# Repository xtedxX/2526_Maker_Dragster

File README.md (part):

# 🏎️ DRAGSTER — Maker Option Project

**A fully custom brushless electric dragster built from scratch: custom PCB, STM32 firmware, 3D-printed chassis and Bluetooth telemetry.**

---

## 📋 Table of Contents

- [Project Overview](#project-overview)
- [System Architecture](#system-architecture)
- [Project Structure](#project-structure)
- [Electronic Design](#electronic-design)
- [Software](#software)
- [3D Modelling and Mechanical Aspect](#3d-modelling-and-mechanical-aspect)
- [Known Issues](#known-issues)

---

## 🚀 Project Overview

This project was carried out as part of the **Maker Option** at school. The goal was to design and build a functional brushless electric dragster entirely from scratch, covering every aspect of the engineering process:

- Custom **4-layer PCB** designed in KiCad
- **STM32G431CBU6** microcontroller firmware written in C with STM32CubeIDE
- **Bluetooth** remote control and telemetry via HC-05
- **3D-printed** chassis and mechanical parts designed in Onshape
- **Brushless motor** driven by a commercial ESC via PWM

---

## 🏗️ System Architecture

### 💡 System Block Diagram

The dragster architecture follows a centralized embedded system design with the STM32G431CBU6 microcontroller managing all peripherals, sensor data acquisition, motor control, and wireless communications.

**Key Subsystems:**
- **Flight Computer**: STM32G431CBU6 (ARM Cortex-M4 @ 170 MHz)
- **Sensor Suite**: MMA8452Q 3-axis accelerometer (I²C interface)
- **Human Interface**: TC1602A 16×2 LCD display + WS2812B RGB LED
- **Communications**: HC-05 Bluetooth 2.0 module (UART interface)
- **Motor Control**: Robitronic Razer Ten ESC with built-in BEC driving 3000kV BLDC motor
- **Power**: LiPo 3S (11.1V) → ESC BEC (5V) → Würth 173950378 LDO (3.3V)

### 🔌 Electrical Schematic Overview

The electrical design emphasizes clean power distribution and proper signal isolation between high-current motor traces and sensitive analog sensors.

**Power Distribution:**
- **11.1V LiPo Battery** → **ESC** (Robitronic Razer Ten with built-in BEC)
- **ESC BEC Output (5V @ 3A)** → Würth 173950378 LDO → **3.3V Logic**
- Motor receives 11.1V directly from battery through ESC
- Separate power planes for motor and logic to minimize EMI

**Signal Integrity:**
- I²C bus: 4.7kΩ pull-ups, 400 kHz operation
- UART: 3.3V logic levels, 9600 baud
- PWM: 50 Hz for ESC, 800 kHz for WS2812B
- SWD debug: dedicated JTAG connector

### 🔩 Mechanical Assembly Overview

The mechanical design prioritizes low center of gravity, rear-wheel drive power transfer, and straight-line stability.

**Component Mounting:**
- **Main Chassis**: Flat PLA plate (base structure)
- **Motor Mount**: Rear bracket aligned with drive pulley
- **PCB Mounting**: Center position for balanced weight distribution
- **Wheel Configuration**: Larger rear wheels for traction, smaller front for steering

---

## 📁 Project Structure

```
DRAGSTER/
│
├── 📖 README.md                        # This file
│
├── 🖼️ IMG/                             # Photos of the physical build
│   ├── dragster_assembled.jpg          # Final assembled dragster
│   ├── system_diagram.svg              # System block diagram
│   ├── electrical_schematic.svg        # Electrical schematic
│   ├── mechanical_assembly.svg         # Mechanical assembly diagram
│   ├── pcb_3d_top.png                  # KiCad 3D render top
│   ├── pcb_3d_bottom.png               # KiCad 3D render bottom
│   ├── pcb_real_top.jpg                # Real PCB top view
│   ├── pcb_real_bottom.jpg             # Real PCB bottom view
│   ├── corps_3d.png                    # Dragster body 3D render
│   ├── support_moteur_3d.png           # Motor mount 3D render
│   ├── support_roues_3d.png            # Wheel axle support 3D render
│   └── guide_roues_3d.png             # Lateral wheel guide 3D render
│
├── 📐 CAO/                             # CAD files and design resources
│   ├── DRAGSTER_Cube_MX/               # STM32CubeMX pin configuration project
│   │   └── DRAGSTER_Cube_MX.ioc        # CubeMX IOC file (pin mapping)
│   ├── DRAGSTER_PCB/                   # KiCad PCB project
│   │   ├── DRAGSTER.kicad_pcb          # PCB layout
│   │   ├── DRAGSTER.kicad_sch          # Schematic
│   │   └── ...
│   └── DRAGSTER_3D/                    # Onshape STL exports
│       ├── Corps.stl                   # Dragster body
│       ├── Support_Moteur.stl          # Motor mount
│       ├── Support_roues.stl           # Camshaft / wheel axle support
│       └── Guide_roues.stl             # Lateral wheel guide
│
└── 💻 DRAGSTER_FIRMWARE/               # STM32CubeIDE project
    └── DRAGSTER/
        ├── Core/
        │   ├── Src/
        │   │   ├── main.c              # Application entry point
        │   │   ├── bldc_esc.c          # ESC / brushless motor driver
        │   │   ├── hc05_bt.c           # Bluetooth driver + command parser
        │   │   ├── mma8452q.c          # Accelerometer driver
        │   │   ├── tc1602a_lcd.c       # LCD driver
        │   │   └── ws2812.c            # NeoPixel LED driver
        │   └── Inc/
        │       ├── bldc_esc.h
        │       ├── hc05_bt.h
        │       ├── mma8452q.h
        │       ├── tc1602a_lcd.h
        │       └── ws2812.h
        └── ...
```

---

## ⚡ Electronic Design

### 🔗 Component Selection & Justification

| Component | Model | Specifications | Engineering Rationale |
|-----------|-------|----------------|----------------------|
| **Microcontroller** | STM32G431CBU6 | ARM Cortex-M4, 170 MHz, UFQFPN48, 128 KB Flash, 32 KB RAM, Hardware FPU | High processing speed for real-time sensor fusion and PWM generation; hardware floating-point unit accelerates velocity integration algorithms; 170 MHz provides sufficient headroom for Bluetooth protocol handling |
| **Brushless Motor** | Robitronic Razer Ten 3652 3000kV (R01230) | 3000 kV, 3652 form factor, 3S LiPo compatible, 350W max power | High kV rating provides aggressive acceleration; 3S compatibility matches battery voltage; compact 3652 size fits dragster chassis constraints |
| **ESC** | Robitronic Razer Ten ESC | PWM control 50 Hz, pulse 1–2 ms, waterproof, 60A continuous, **Built-in BEC: 5V @ 3A** | Standard RC PWM interface simplifies firmware; 60A rating provides safety margin for peak current draws; waterproof design protects against track debris; **Built-in BEC eliminates need for separate buck converter — provides 5V power rail for logic** |
| **Accelerometer** | MMA8452Q | 3-axis, 12-bit resolution, I²C interface, ±8g range, 800 Hz ODR, embedded FIFO | ±8g range captures full dragster launch dynamics; 800 Hz sampling rate prevents aliasing of high-frequency vibrations; I²C interface reduces pin count; FIFO buffer offloads MCU during burst acceleration |
| **LCD Display** | TC1602A | 16×2 characters, HD44780 controller, 4-bit parallel interface, 5V tolerant | Industry-standard HD44780 ensures driver compatibility; 4-bit mode saves GPIO pins; 16×2 layout accommodates speed/peak display; high contrast for outdoor visibility |
| **Bluetooth Module** | HC-05 | Bluetooth 2.0 Classic SPP, UART interface, 9600 baud default, 3.3V logic, 10m range | Serial Port Profile (SPP) enables simple UART passthrough; 9600 baud sufficient for telemetry bandwidth; 3.3V logic compatible with STM32 GPIO; widely supported by PC/Android terminals |
| **RGB LED** | WS2812B | Addressable RGB, 800 kHz PWM protocol, 5V supply, single-wire control | Addressable interface allows dynamic status indication; single-wire protocol minimizes pin usage; built-in PWM drivers offload MCU; **Note**: 5V requirement conflicts with 3.3V board supply |
| **Battery** | LiPo 3S | 11.1V nominal (12.6V max, 9V min), 2200 mAh capacity, 25C discharge | 3S voltage matches motor/ESC specifications; 2200 mAh provides ~5 min runtime at full throttle; 25C discharge rating (55A burst) exceeds motor peak current |
| **Voltage Regulator (LDO)** | Würth 173950378 | Input: 4.5–5.5V, Output: 3.3V @ 1A, Dropout: 150mV, Low noise | Converts 5V from ESC BEC to 3.3V logic level; low dropout ensures stable 3.3V even when 5V sags; low noise critical for ADC and analog sensors; compact SOT-23-5 package |
| **Polarity Protection** | SQ2389CES-T1_GE3 | P-channel MOSFET, -20V Vds, -8A Id, 25 mΩ Rds(on) | Low on-resistance minimizes voltage drop; automotive-grade robustness; **Note**: Not populated on final board |

### 📋 PCB Design

The PCB was designed entirely from scratch using **KiCad 9.0**. Before layout, **STM32CubeMX** was used to plan and verify peripheral pin assignments, ensuring no resource conflicts.

**CubeMX Configuration File:**
```
CAO/DRAGSTER_Cube_MX/DRAGSTER_Cube_MX.ioc
```

#### PCB Specifications

| Parameter | Value | Engineering Notes |
|-----------|-------|------------------|
| **Dimensions** | 60 mm × 60 mm | Square form factor simplifies chassis mounting; fits within dragster width constraints |
| **Layer Count** | 4 layers | Minimum for proper power/ground plane separation |
| **Layer 1 (Top)** | Signal routing | Component-side traces, I²C/UART/GPIO |
| **Layer 2 (Inner)** | Ground plane | Solid copper pour, minimal voids, return path for all signals |
| **Layer 3 (Inner)** | Power plane | Split 5V/3.3V regions, thermal relief for vias |
| **Layer 4 (Bottom)** | Signal routing | Secondary traces, connector breakouts |
| **Copper Weight** | 1 oz (35 µm) | Standard weight, adequate for logic-level currents |
| **Min Track/Gap** | 6/6 mil (0.15 mm) | JLCPCB standard capability |
| **Via Size** | 0.3 mm drill, 0.6 mm pad | Standard via, thermal/signal transfer |
| **Manufacturer** | JLCPCB | 4-day turnaround, cost-effective for prototyping |

**Stackup Advantages:**
- Dedicated ground plane (Layer 2) provides low-impedance return path for high-speed PWM signals
- Power plane (Layer 3) reduces supply inductance and decoupling requirements
- Four-layer design enables controlled impedance routing (not critical at these speeds but improves margin)
- Ground plane shields sensitive I²C traces from motor PWM noise

#### KiCad 3D Renders

**Top Layer (Component Side):**

**Component Placement:**
- **Center**: STM32G431CBU6 (UFQFPN-48 package, 7×7 mm)
- **Top-Left**: MMA8452Q accelerometer (QFN-16, oriented with X-axis parallel to chassis)
- **Top-Right**: Würth 173950378 LDO regulator (5V to 3.3V conversion)
- **Bottom-Left**: HC-05 Bluetooth module connector (6-pin header)
- **Bottom-Right**: LCD interface connector (8-pin header: 4 data + RS/E/VCC/GND)
- **Right Edge**: ESC PWM output (3-pin servo connector) + 5V BEC input from ESC
- **Left Edge**: JTAG/SWD debug header (10-pin Cortex standard)

**Bottom Layer (Connector Side):**

**Features:**
- Battery input connector (JST XH 2S/3S balance plug compatible)
- NeoPixel LED footprint (currently unpopulated due to voltage mismatch)
- Reverse polarity protection MOSFET footprint (designed but not populated)
- Ground test points for oscilloscope probing

#### Real PCB Photos

**Fabricated Top Layer:**

**Fabricated Bottom Layer:**

**Fully Assembled Board:**

**Assembly Notes:**
- All SMD components hand-soldered using hot air rework station and an oven
- UFQFPN-48 package required careful alignment and flux application
- 0402 resistors/capacitors used for space efficiency
- Through-hole connectors added last to prevent mechanical stress during SMD soldering

---

## 💻 Software

### 📐 Pin Assignment — STM32CubeMX

Before writing any firmware, **STM32CubeMX** was used to configure the clock tree, assign peripheral pins, and verify that no resource conflicts existed. This tool generates the HAL initialization code automatically, ensuring consistency between hardware and software.

**CubeMX Configuration:**
```
CAO/DRAGSTER_Cube_MX/DRAGSTER_Cube_MX.ioc
```

#### Peripheral Pin Mapping

| Peripheral | Pins | Function | Configuration |
|------------|------|----------|---------------|
| **I2C1** | PA15 (SCL), PB7 (SDA) | MMA8452Q accelerometer communication | 400 kHz fast mode, 7-bit addressing, repeated start enabled |
| **USART2** | PA2 (TX), PA3 (RX) | HC-05 Bluetooth module | 9600 baud, 8N1, RX interrupt-driven |
| **USART1** | PA9 (TX), PA10 (RX) | ST-Link debug console output | 115200 baud, 8N1, polling mode |
| **TIM3 CH1** | PA6 | ESC PWM signal generation | 50 Hz (20 ms period), 1-2 ms pulse width |
| **TIM2 CH4** | PB11 | WS2812B NeoPixel DMA PWM | 800 kHz bit encoding via DMA circular buffer |
| **GPIO Output** | PA8 | LCD RS (Register Select) | Push-pull, high speed |
| **GPIO Output** | PC6 | LCD E (Enable strobe) | Push-pull, high speed |
| **GPIO Output** | PB12–PB15 | LCD DB4–DB7 (4-bit data) | Push-pull, high speed |
| **GPIO Input** | PC13 | Accelerometer INT1 (data ready) | Pull-down, EXTI interrupt (unused in polling implementation) |
| **GPIO Input** | PB9 | Accelerometer INT2 (motion detect) | Pull-down, EXTI interrupt (unused) |

**Clock Configuration:**
- **HSE**: 16 MHz external crystal oscillator
- **PLL**: Input 16 MHz → PLLM /1 → VCO 680 MHz → PLLN ×85 → PLLP /4 → **170 MHz System Clock**
- **APB1**: 85 MHz (TIM2/3 at 170 MHz after prescaler doubling)
- **APB2**: 170 MHz (high-speed peripherals)
- **AHB**: 170 MHz (CPU, DMA, memory)

---

### 🗂️ Firmware Architecture

```
DRAGSTER_FIRMWARE/DRAGSTER/Core/
│
├── Src/
│   ├── main.c              # Application entry point and main loop
│   ├── bldc_esc.c          # Brushless motor ESC PWM driver
│   ├── hc05_bt.c           # HC-05 Bluetooth UART driver and command parser
│   ├── mma8452q.c          # MMA8452Q I²C accelerometer driver
│   ├── tc1602a_lcd.c       # TC1602A LCD parallel interface driver
│   └── ws2812.c            # WS2812B NeoPixel DMA PWM driver (non-functional)
│
└── Inc/
    ├── bldc_esc.h          # ESC API and configuration macros
    ├── hc05_bt.h           # Bluetooth handle and command definitions
    ├── mma8452q.h          # Accelerometer register map and API
    ├── tc1602a_lcd.h       # LCD command macros and API
    └── ws2812.h            # NeoPixel color encoding and API
```

---

### 📦 Software Module Descriptions

#### `main.c` — Application Entry Point

**Responsibilities:**
- HAL library initialization
- System clock configuration (170 MHz)
- Peripheral initialization (GPIO, DMA, timers, UARTs, I²C)
- Boot sequence orchestration
- Main event loop execution

**Boot Sequence:**
1. `HAL_Init()` — Initialize HAL library and configure SysTick timer
2. `SystemClock_Config()` — Configure PLL to achieve 170 MHz system clock
3. `MX_GPIO_Init()` — Configure GPIO pins (LCD control, LEDs, debug)
4. `MX_DMA_Init()` — Initialize DMA channels for TIM2 PWM (NeoPixel)
5. `MX_I2C1_Init()` — Configure I²C1 at 400 kHz for accelerometer
6. `MX_TIM2_Init()` — Configure TIM2 for 800 kHz NeoPixel PWM
7. `MX_TIM3_Init()` — Configure TIM3 for 50 Hz ESC PWM
8. `MX_USART1_UART_Init()` — Configure debug UART at 115200 baud
9. `MX_USART2_UART_Init()` — Configure Bluetooth UART at 9600 baud
10. **`HAL_TIM_PWM_Start(&htim3, TIM_CHANNEL_1)`** — **CRITICAL**: Start ESC PWM immediately (ESC expects signal within 2 seconds of power-on)
11. `LCD_Splash()` — Display boot logo on LCD ("DRAGSTER v1.0")
12. `MMA8452Q_Init()` — Initialize accelerometer (±8g range, 800 Hz ODR)
13. `BT_Init()` — Initialize Bluetooth driver and enable RX interrupt
14. `ESC_Init()` — Execute ESC arming sequence (~8 seconds, blocking)
15. **Main Loop** — `while(1)` calls `BT_Task()` and updates LCD with accelerometer data

**Main Loop Structure:**
```c
while (1) {
    BT_Task();  // Process Bluetooth commands, send telemetry
    
    // Read accelerometer X-axis
    float accel_x_g = MMA8452Q_ReadAccelX();
    
    // Integrate to compute speed (trapezoidal rule)
    static float prev_accel = 0.0f;
    float dt = 0.01f;  // 100 Hz loop rate (approximate)
    speed_ms += (accel_x_g + prev_accel) / 2.0f * 9.81f * dt;
    prev_accel = accel_x_g;
    
    // Update LCD display
    LCD_PrintSpeed(speed_ms * 3.6f);  // Convert m/s to km/h
    LCD_PrintPeakSpeed(peak_speed_kmh);
    
    HAL_Delay(10);  // 100 Hz update rate
}
```

---

#### `bldc_esc.c` / `bldc_esc.h` — ESC PWM Driver

**Purpose:** Generate precise 50 Hz PWM signals to control the Robitronic Razer Ten ESC, which in turn drives the brushless motor.

**Timer Configuration:**
- **Timer**: TIM3 Channel 1 (PA6)
- **Prescaler (PSC)**: 169 → Timer clock = 170 MHz / 170 = **1 MHz** (1 tick = 1 µs)
- **Auto-Reload (ARR)**: 19999 → Period = 20000 µs = **20 ms** = **50 Hz**
- **Pulse Width Range**: 1000–2000 µs (standard RC servo range)

**Verified PWM Values:**

| Compare Value | Pulse Width | Duty Cycle | Throttle | ESC Behavior |
|---------------|-------------|------------|----------|--------------|
| `199` | 200 µs | 1% | 0% | Minimum throttle (motor off) |
| `2999` | 3000 µs | 15% | 50% | Neutral (used during arming only) |
| `9999` | 10000 µs | 50% | 100% | Maximum throttle (full power) |

**Note:** ESC interprets pulse widths, not duty cycle percentages. The unusual mapping (200 µs = 0%, 10000 µs = 100%) is ESC-specific.

**ESC Arming Sequence** (empirically determined):
1. **Step 1** (4 s): Send 3000 µs pulse → ESC beeps twice, recognizes calibration range
2. **Step 2** (2 s): Send 200 µs pulse → ESC beeps three times, arms motor controller
3. **Step 3** (2 s): Send 3000 µs pulse → ESC ready, motor can now be controlled

**Total arming time**: ~8 seconds (blocking operation during boot)

**API Functions:**

| Function | Parameters | Description |
|----------|-----------|-------------|
| `ESC_Init()` | `void` | Executes the 3-step arming sequence. PWM must already be running via `HAL_TIM_PWM_Start()` before calling. Blocking for 8 seconds. |
| `ESC_SetThrottlePct(pct)` | `uint8_t pct` (0–100) | Sets throttle as percentage. Internally maps to 200–10000 µs pulse range via linear interpolation. |
| `ESC_SetPulse(pulse_us)` | `uint16_t pulse_us` | Directly sets PWM compare value (200–10000 µs). Bypasses percentage mapping for advanced control. |
| `ESC_Stop()` | `void` | Immediately sets throttle to 0% (200 µs pulse). Emergency stop function. |
| `ESC_RampTo(pct, step_ms)` | `uint8_t pct`, `uint16_t step_ms` | Gradually increases or decreases throttle to target percentage with specified step delay. Blocking function. Prevents abrupt torque changes that could flip the dragster. |

**Configuration Macros** (`bldc_esc.h`):
```c
#define ESC_PULSE_MIN_US    199U    // 0% throttle (actually 200 µs, off-by-one from rounding)
#define ESC_PULSE_MAX_US    9999U   // 100% throttle (10000 µs)
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
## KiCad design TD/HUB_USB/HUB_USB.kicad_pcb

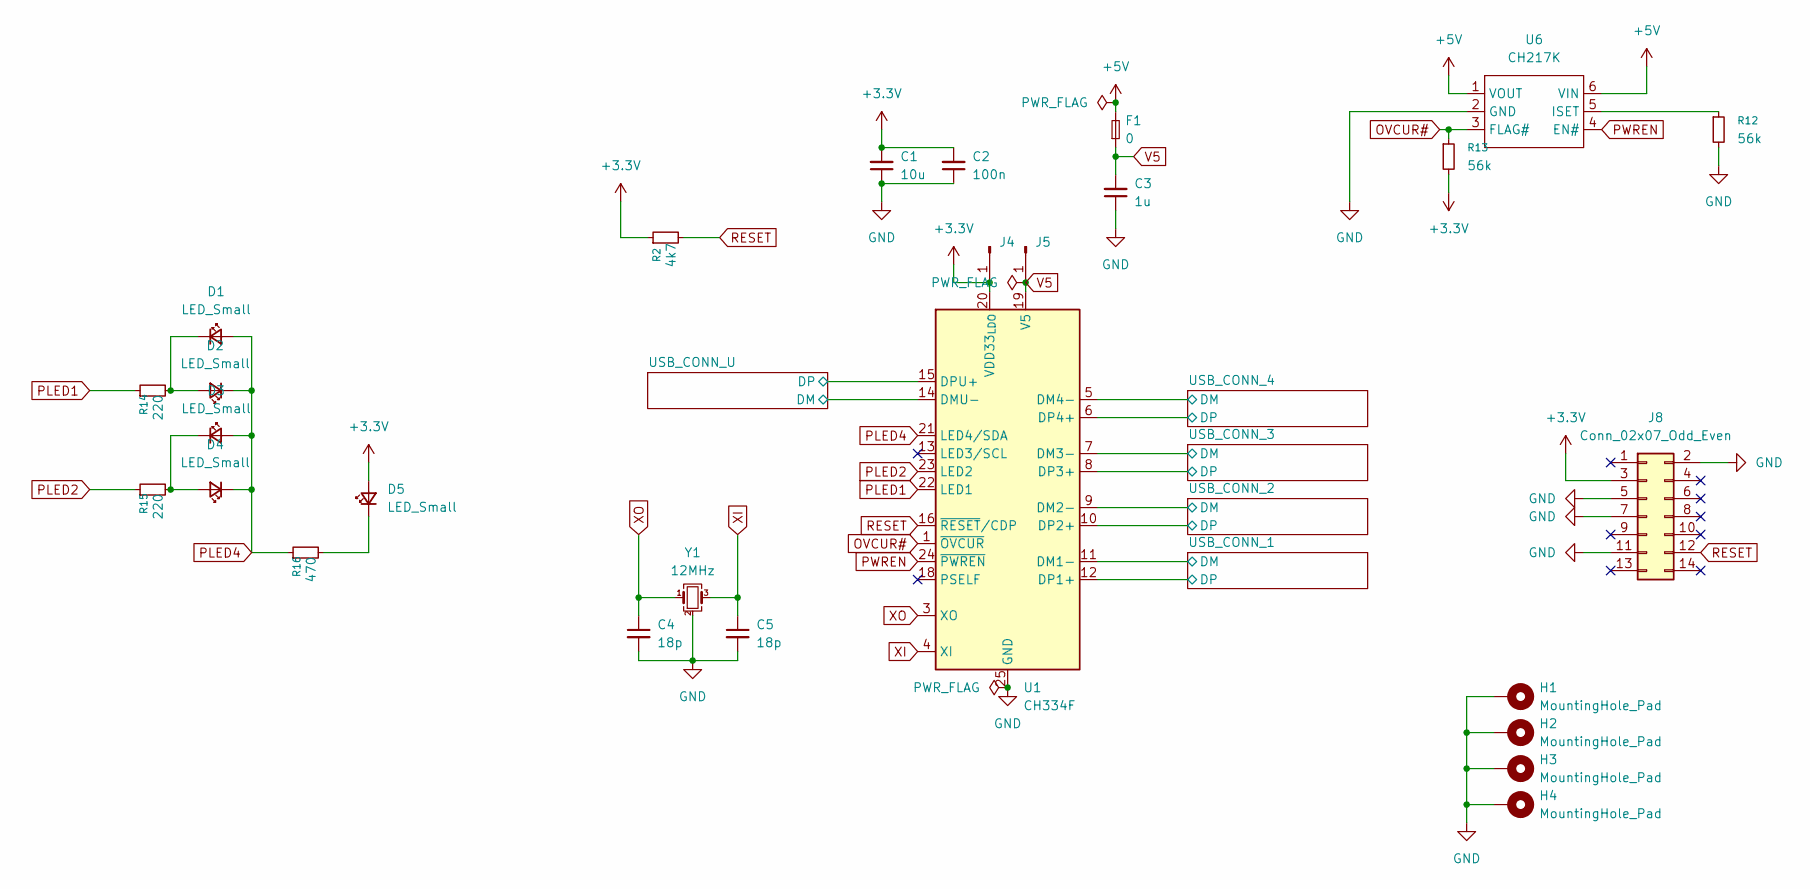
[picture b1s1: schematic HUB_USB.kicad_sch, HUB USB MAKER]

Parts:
C1: 10u; C_0402_1005Metric; MPN GRM155R60J106ME18D
C2: 100n; C_0402_1005Metric; MPN GXT155R71E104KE01D
C3: 1u; C_0603_1608Metric; MPN KGM15BS60J105KT
C4, C5: 18p; C_0402_1005Metric; MPN VJ0402D180FXCAJ
D1, D2, D3, D4, D5: LED_Small; LED_0603_1608Metric; MPN LSM0603453V
F1: 0; Fuse_1206_3216Metric; MPN SF-1206SA2000R-2
H1, H2, H3, H4: MountingHole_Pad; MountingHole_2.7mm_M2.5_Pad_Via
J4, J5: Conn_01x01_Pin; TestPoint_Pad_D1.5mm; MPN CPG-62-TH-TR
J8: Conn_02x07_Odd_Even; PinHeader_2x07_P1.27mm_Vertical_SMD; MPN 10129381-914001BLF
R2: 4k7; R_0402_1005Metric; MPN RCA04024K70JNED
R12, R13: 56k; R_0805_2012Metric; MPN KTR10EZPF5602
R14, R15: 220; R_0402_1005Metric; MPN KTR25JZPF2200
R16: 470; R_0603_1608Metric; MPN PTN0603E4700BST1
U1: CH334F; QFN-24-1EP_4x4mm_P0.5mm_EP2.7x2.7mm; MPN 5997
U6: CH217K; SOT-23-6; MPN CH217K
Y1: 12MHz; Crystal_SMD_WE_CFPX-104-4Pin_5.0x3.2mm; MPN 830036401

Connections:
+3.3V: C1.2, C2.2, D5.2 (A), J4.1, J8.3, R2.1, R13.2, U1.20 (VDD33_{LDO})
+5V: F1.2, U6.1 (VOUT), U6.6 (VIN); also elsewhere on the board
/USB_CONN_1/DM: U1.11 (DM1-); also elsewhere on the board
/USB_CONN_1/DP: U1.12 (DP1+); also elsewhere on the board
/USB_CONN_2/DM: U1.9 (DM2-); also elsewhere on the board
/USB_CONN_2/DP: U1.10 (DP2+); also elsewhere on the board
/USB_CONN_3/DM: U1.7 (DM3-); also elsewhere on the board
/USB_CONN_3/DP: U1.8 (DP3+); also elsewhere on the board
/USB_CONN_4/DM: U1.5 (DM4-); also elsewhere on the board
/USB_CONN_4/DP: U1.6 (DP4+); also elsewhere on the board
/USB_CONN_U/DM: U1.14 (DMU-); also elsewhere on the board
/USB_CONN_U/DP: U1.15 (DPU+); also elsewhere on the board
GND: C1.1, C2.1, C3.1, C4.2, C5.2, H1.1, H2.1, H3.1, H4.1, J8.2, J8.5, J8.7, J8.11, R12.2, U1.25 (GND), U6.2 (GND), Y1.2 (G), Y1.4 (G); also elsewhere on the board
unnamed: D1.1 (K), D2.2 (A), R14.2
unnamed: D3.1 (K), D4.2 (A), R15.2
unnamed: D5.1 (K), R16.2
unnamed: R12.1, U6.5 (ISET)
OVCUR#: R13.1, U1.1 (~OVCUR), U6.3 (FLAG#)
PLED1: R14.1, U1.22 (LED1)
PLED2: R15.1, U1.23 (LED2)
PLED4: D1.2 (A), D2.1 (K), D3.2 (A), D4.1 (K), R16.1, U1.21 (LED4/SDA)
PWREN: U1.24 (~PWREN), U6.4 (EN#)
RESET: J8.12, R2.2, U1.16 (~RESET/CDP)
V5: C3.2, F1.1, J5.1, U1.19 (V5)
XI: C5.1, U1.4 (XI), Y1.3
XO: C4.1, U1.3 (XO), Y1.1

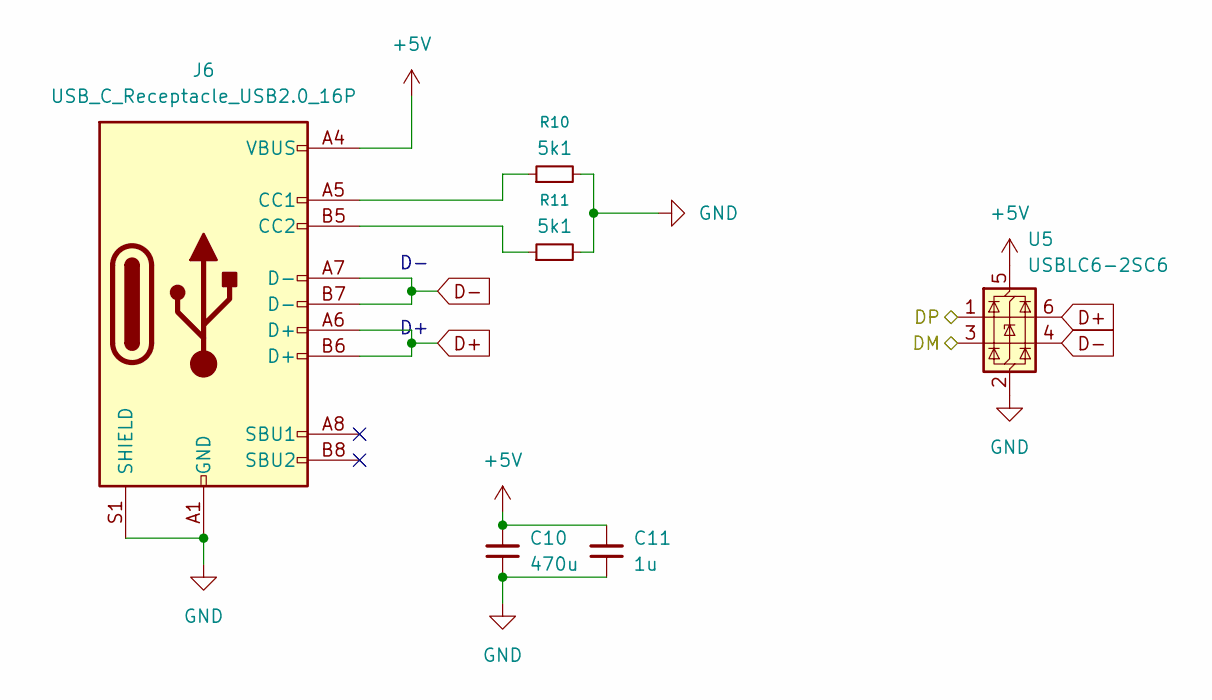
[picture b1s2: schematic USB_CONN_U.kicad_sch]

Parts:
C10: 470u; CP_Elec_6.3x9.9; MPN APZ0609471M010R
C11: 1u; C_0603_1608Metric; MPN KGM15BS60J105KT
J6: USB_C_Receptacle_USB2.0_16P; USB_C_Receptacle_Palconn_UTC16-G; MPN 217179-0001
R10, R11: 5k1; R_0603_1608Metric; MPN TNPW06035K11BYEN
U5: USBLC6-2SC6; SOT-23-6; MPN USBLC6-2SC6

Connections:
+5V: C10.2, C11.2, J6.A4 (VBUS), J6.A9 (VBUS), J6.B4 (VBUS), J6.B9 (VBUS), U5.5 (VBUS); also elsewhere on the board
/USB_CONN_U/DM: U5.3 (I/O2); also elsewhere on the board
/USB_CONN_U/DP: U5.1 (I/O1); also elsewhere on the board
D+: J6.A6 (D+), J6.B6 (D+), U5.6 (I/O1); also elsewhere on the board
D-: J6.A7 (D-), J6.B7 (D-), U5.4 (I/O2); also elsewhere on the board
GND: C10.1, C11.1, J6.A1 (GND), J6.A12 (GND), J6.B1 (GND), J6.B12 (GND), J6.S1 (SHIELD), R10.2, R11.2, U5.2 (GND); also elsewhere on the board
unnamed: J6.A5 (CC1), R10.1
unnamed: J6.B5 (CC2), R11.1

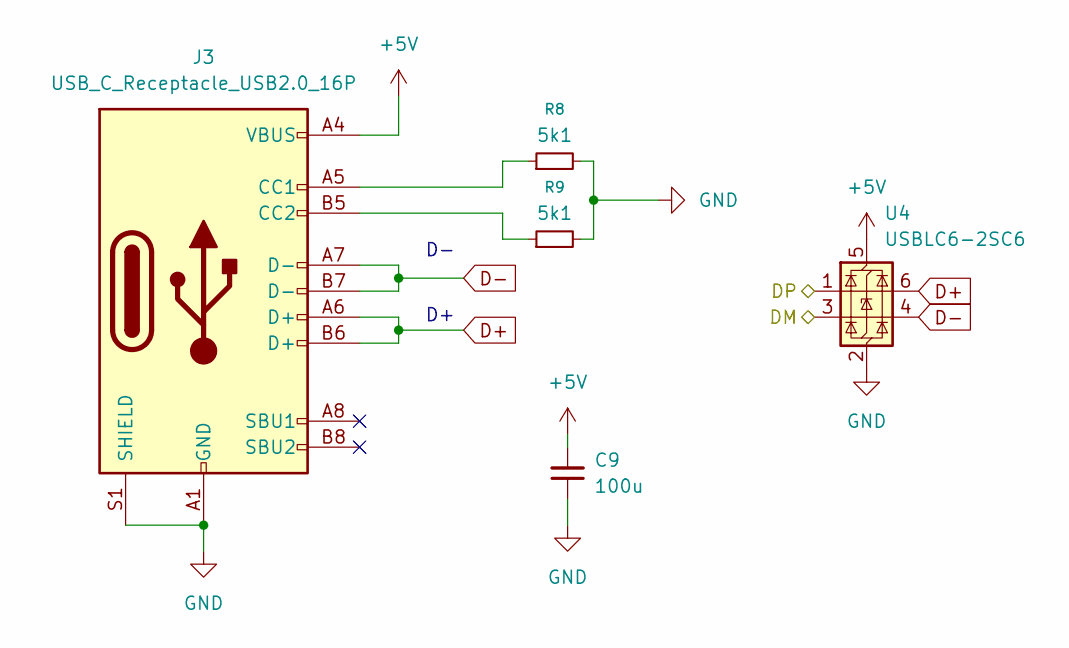
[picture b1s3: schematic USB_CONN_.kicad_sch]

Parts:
C9: 100u; C_1206_3216Metric; MPN KGM31HR50J107MU
J3: USB_C_Receptacle_USB2.0_16P; USB_C_Receptacle_Palconn_UTC16-G; MPN 217179-0001
R8, R9: 5k1; R_0603_1608Metric; MPN TNPW06035K11BYEN
U4: USBLC6-2SC6; SOT-23-6; MPN USBLC6-2SC6

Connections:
+5V: C9.2, J3.A4 (VBUS), J3.A9 (VBUS), J3.B4 (VBUS), J3.B9 (VBUS), U4.5 (VBUS); also elsewhere on the board
/USB_CONN_4/DM: U4.3 (I/O2); also elsewhere on the board
/USB_CONN_4/DP: U4.1 (I/O1); also elsewhere on the board
D+: J3.A6 (D+), J3.B6 (D+), U4.6 (I/O1); also elsewhere on the board
D-: J3.A7 (D-), J3.B7 (D-), U4.4 (I/O2); also elsewhere on the board
GND: C9.1, J3.A1 (GND), J3.A12 (GND), J3.B1 (GND), J3.B12 (GND), J3.S1 (SHIELD), R8.2, R9.2, U4.2 (GND); also elsewhere on the board
unnamed: J3.A5 (CC1), R8.1
unnamed: J3.B5 (CC2), R9.1

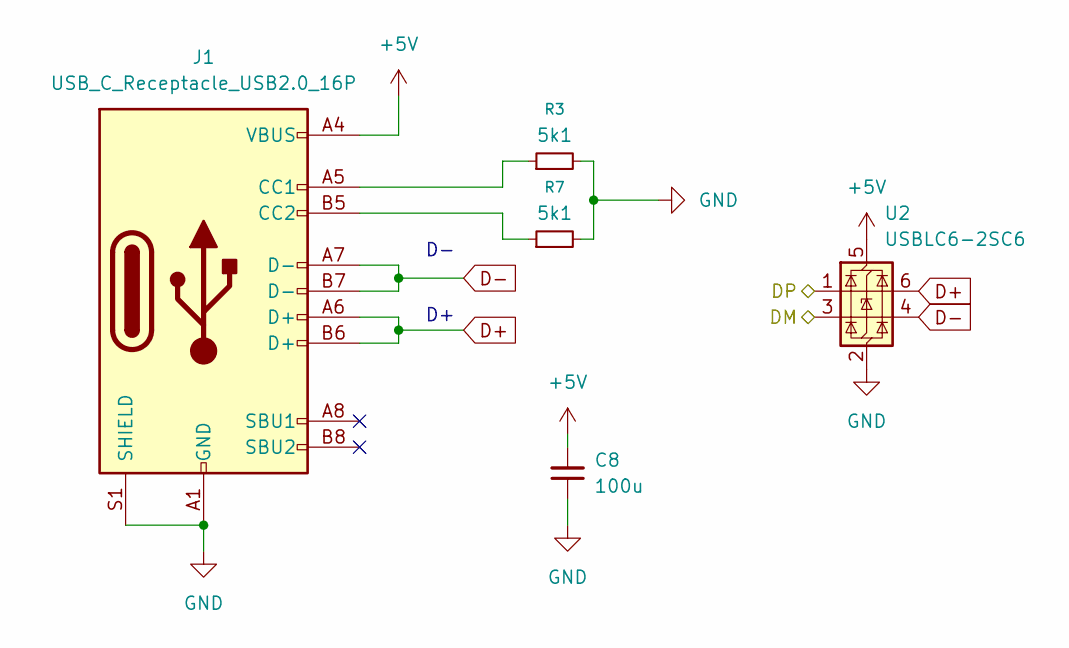
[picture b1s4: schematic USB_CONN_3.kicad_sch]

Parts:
C8: 100u; C_1206_3216Metric; MPN KGM31HR50J107MU
J1: USB_C_Receptacle_USB2.0_16P; USB_C_Receptacle_Palconn_UTC16-G; MPN 217179-0001
R3, R7: 5k1; R_0603_1608Metric; MPN TNPW06035K11BYEN
U2: USBLC6-2SC6; SOT-23-6; MPN USBLC6-2SC6

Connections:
+5V: C8.2, J1.A4 (VBUS), J1.A9 (VBUS), J1.B4 (VBUS), J1.B9 (VBUS), U2.5 (VBUS); also elsewhere on the board
/USB_CONN_3/DM: U2.3 (I/O2); also elsewhere on the board
/USB_CONN_3/DP: U2.1 (I/O1); also elsewhere on the board
D+: J1.A6 (D+), J1.B6 (D+), U2.6 (I/O1); also elsewhere on the board
D-: J1.A7 (D-), J1.B7 (D-), U2.4 (I/O2); also elsewhere on the board
GND: C8.1, J1.A1 (GND), J1.A12 (GND), J1.B1 (GND), J1.B12 (GND), J1.S1 (SHIELD), R3.2, R7.2, U2.2 (GND); also elsewhere on the board
unnamed: J1.A5 (CC1), R3.1
unnamed: J1.B5 (CC2), R7.1

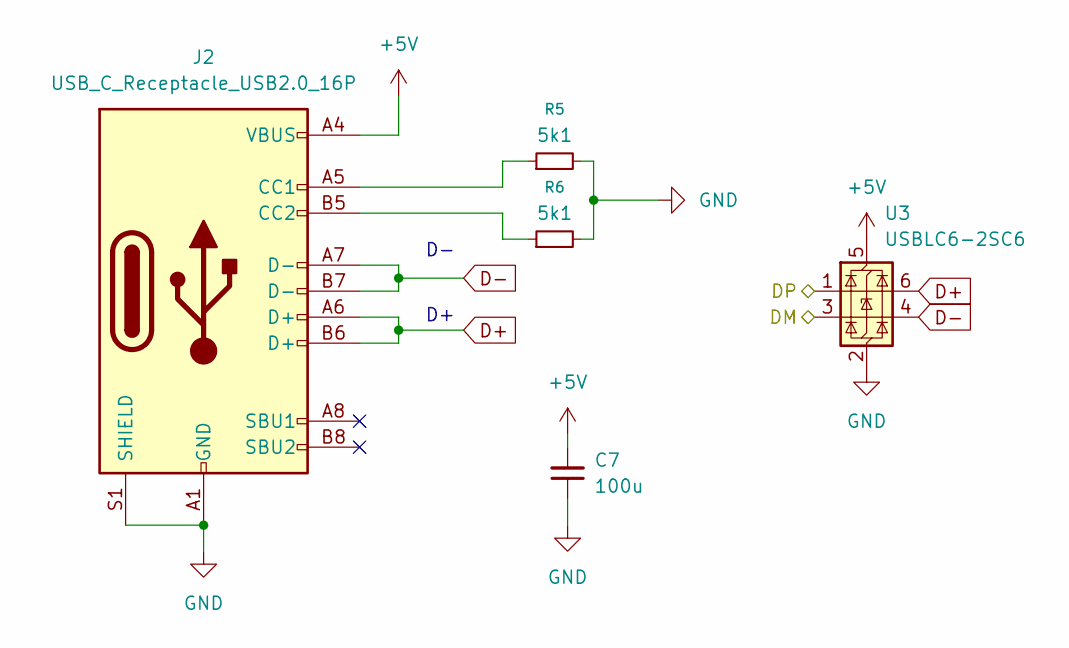
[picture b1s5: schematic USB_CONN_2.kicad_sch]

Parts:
C7: 100u; C_1206_3216Metric; MPN KGM31HR50J107MU
J2: USB_C_Receptacle_USB2.0_16P; USB_C_Receptacle_Palconn_UTC16-G; MPN 217179-0001
R5, R6: 5k1; R_0603_1608Metric; MPN TNPW06035K11BYEN
U3: USBLC6-2SC6; SOT-23-6; MPN USBLC6-2SC6

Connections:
+5V: C7.2, J2.A4 (VBUS), J2.A9 (VBUS), J2.B4 (VBUS), J2.B9 (VBUS), U3.5 (VBUS); also elsewhere on the board
/USB_CONN_2/DM: U3.3 (I/O2); also elsewhere on the board
/USB_CONN_2/DP: U3.1 (I/O1); also elsewhere on the board
D+: J2.A6 (D+), J2.B6 (D+), U3.6 (I/O1); also elsewhere on the board
D-: J2.A7 (D-), J2.B7 (D-), U3.4 (I/O2); also elsewhere on the board
GND: C7.1, J2.A1 (GND), J2.A12 (GND), J2.B1 (GND), J2.B12 (GND), J2.S1 (SHIELD), R5.2, R6.2, U3.2 (GND); also elsewhere on the board
unnamed: J2.A5 (CC1), R5.1
unnamed: J2.B5 (CC2), R6.1

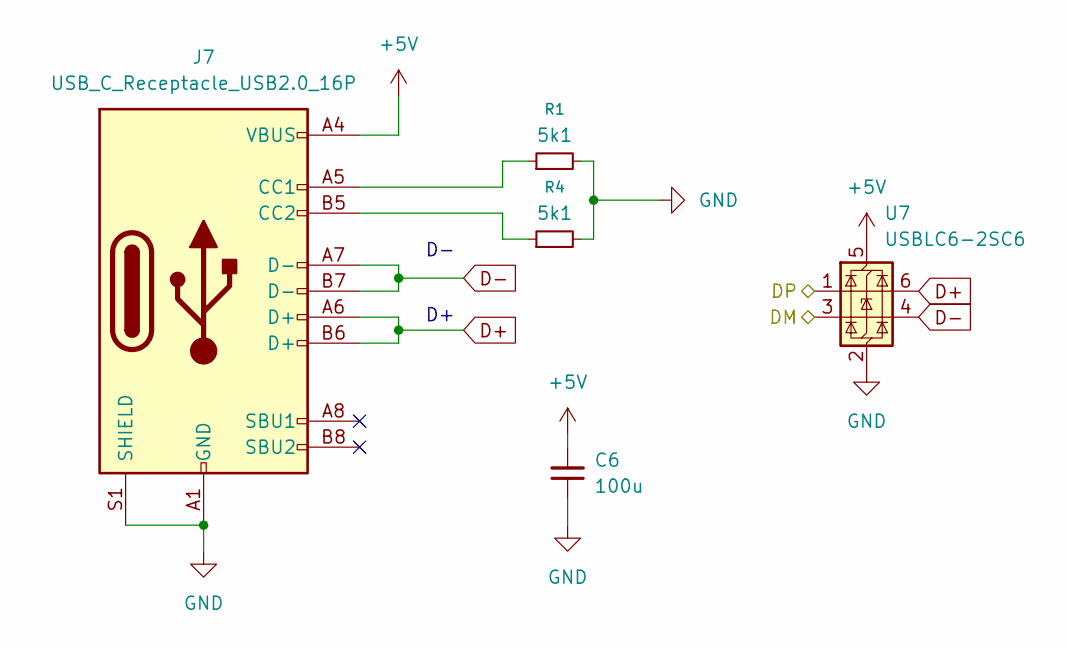
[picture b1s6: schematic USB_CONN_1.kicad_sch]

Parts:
C6: 100u; C_1206_3216Metric; MPN KGM31HR50J107MU
J7: USB_C_Receptacle_USB2.0_16P; USB_C_Receptacle_Palconn_UTC16-G; MPN 217179-0001
R1, R4: 5k1; R_0603_1608Metric; MPN TNPW06035K11BYEN
U7: USBLC6-2SC6; SOT-23-6; MPN USBLC6-2SC6

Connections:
+5V: C6.2, J7.A4 (VBUS), J7.A9 (VBUS), J7.B4 (VBUS), J7.B9 (VBUS), U7.5 (VBUS); also elsewhere on the board
/USB_CONN_1/DM: U7.3 (I/O2); also elsewhere on the board
/USB_CONN_1/DP: U7.1 (I/O1); also elsewhere on the board
D+: J7.A6 (D+), J7.B6 (D+), U7.6 (I/O1); also elsewhere on the board
D-: J7.A7 (D-), J7.B7 (D-), U7.4 (I/O2); also elsewhere on the board
GND: C6.1, J7.A1 (GND), J7.A12 (GND), J7.B1 (GND), J7.B12 (GND), J7.S1 (SHIELD), R1.2, R4.2, U7.2 (GND); also elsewhere on the board
unnamed: J7.A5 (CC1), R1.1
unnamed: J7.B5 (CC2), R4.1

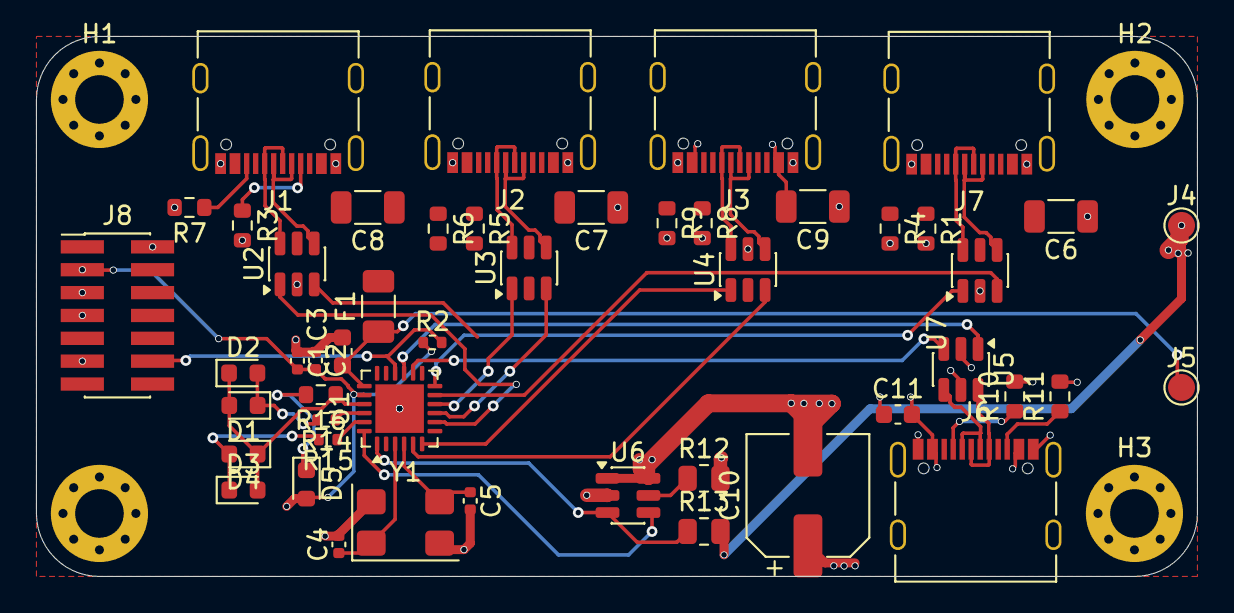
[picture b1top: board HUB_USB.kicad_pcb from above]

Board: 4 copper layers, 64.5 x 30.0 mm, 53 parts (0 on the bottom side), 38 nets.

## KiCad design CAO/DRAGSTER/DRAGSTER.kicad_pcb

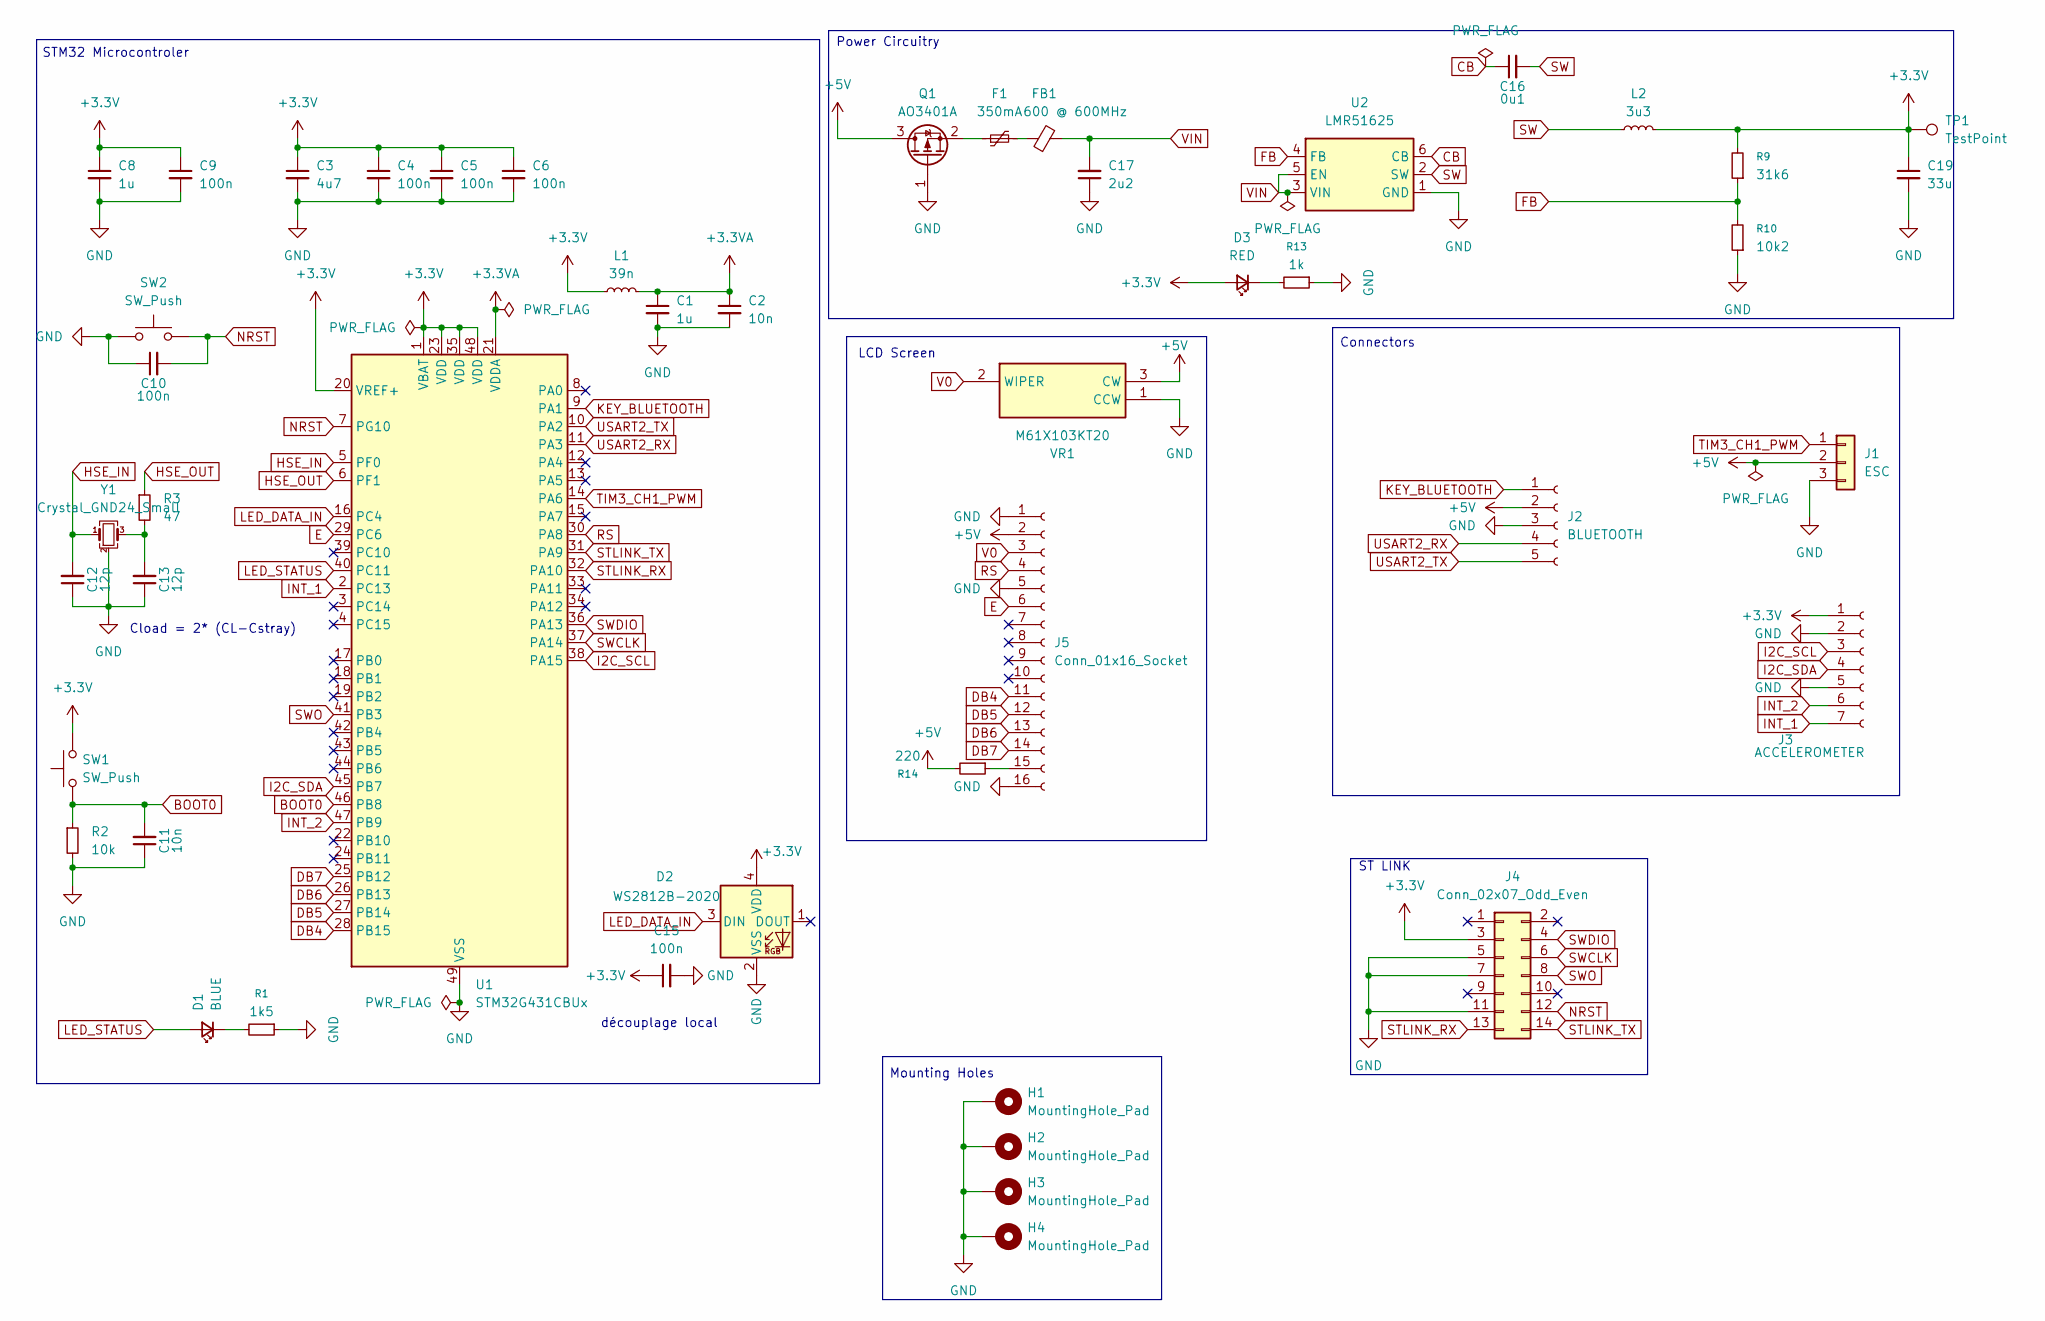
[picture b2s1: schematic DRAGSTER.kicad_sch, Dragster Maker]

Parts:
C1, C8: 1u; C_0402_1005Metric_Pad0.74x0.62mm_HandSolder; MPN GXT155R60J105KE01D
C2, C11: 10n; C_0402_1005Metric_Pad0.74x0.62mm_HandSolder; MPN GRM155R70J103KA01D
C3: 4u7; C_0402_1005Metric_Pad0.74x0.62mm_HandSolder; MPN MCASJ105BB5475MFNA1J
C4, C5, C6, C9, C10, C15: 100n; C_0402_1005Metric_Pad0.74x0.62mm_HandSolder; MPN 04026C104MAT2A
C12, C13: 12p; C_0402_1005Metric_Pad0.74x0.62mm_HandSolder; MPN 0402YA120JAT2A
C16: 0u1; C_0603_1608Metric_Pad1.08x0.95mm_HandSolder; MPN CC0603KRX7R8BB104
C17: 2u2; C_1206_3216Metric_Pad1.33x1.80mm_HandSolder; MPN KGM31HR71C225KU
C19: 33u; C_2220_5750Metric_Pad1.97x5.40mm_HandSolder; MPN CKG57NX7R1C336M500JH
D1: BLUE; LED_0402_1005Metric_Pad0.77x0.64mm_HandSolder; MPN 599-1A90-147F
D2: WS2812B-2020; LED_WS2812B-2020_PLCC4_2.0x2.0mm; MPN 150044M155260
D3: RED; LED_0402_1005Metric_Pad0.77x0.64mm_HandSolder; MPN SML-P12UTT86R
F1: 350mA; Fuse_0402_1005Metric_Pad0.77x0.64mm_HandSolder
FB1: 600 @ 600MHz; L_0402_1005Metric_Pad0.77x0.64mm_HandSolder
H1, H2, H3, H4: MountingHole_Pad; MountingHole_4.3mm_M4_Pad_Via
J1: ESC; PinHeader_1x03_P1.27mm_Vertical
J2: BLUETOOTH; PinSocket_1x05_P2.00mm_Horizontal
J3: ACCELEROMETER; PinSocket_1x07_P2.00mm_Vertical
J4: Conn_02x07_Odd_Even; PinHeader_2x07_P2.54mm_Vertical_SMD
J5: Conn_01x16_Socket; PinSocket_1x16_P2.00mm_Vertical
L1: 39n; L_0402_1005Metric_Pad0.77x0.64mm_HandSolder; MPN LQG15HS39NH02D
L2: 3u3; 78439369033; MPN 78439369033
Q1: AO3401A; SOT-23; MPN SQ2389CES-T1_GE3
R1: 1k5; R_0402_1005Metric_Pad0.72x0.64mm_HandSolder; MPN 4D02WGJ0152TCE
R2: 10k; R_0402_1005Metric_Pad0.72x0.64mm_HandSolder; MPN 4D02WGF1002TCE
R3: 47; R_0402_1005Metric_Pad0.72x0.64mm_HandSolder; MPN 4D02WGF470JTCE
R9: 31k6; R_0402_1005Metric_Pad0.72x0.64mm_HandSolder; MPN CRT0402-BY-3162GLF
R10: 10k2; R_0402_1005Metric_Pad0.72x0.64mm_HandSolder; MPN ERA-2VPB1022X
R13: 1k; R_0402_1005Metric_Pad0.72x0.64mm_HandSolder; MPN RC0402JR-7D1KL
R14: 220; R_0402_1005Metric_Pad0.72x0.64mm_HandSolder; MPN ERA-2ARB221X
SW1, SW2: SW_Push; 15715636; MPN 1571563-6
TP1: TestPoint; TestPoint_Pad_1.5x1.5mm
U1: STM32G431CBUx; QFN-48-1EP_7x7mm_P0.5mm_EP5.6x5.6mm; MPN STM32G431CBU6
U2: LMR51625; SOT-23-6; MPN LMR51625XDDCR
VR1: M61X103KT20; Manufacturer_Part_Number M61X103KT20
Y1: Crystal_GND24_Small; LFXTAL071744Reel; MPN LFXTAL071744Reel

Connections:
+3.3V: C3.1, C4.1, C5.1, C6.1, C8.1, C9.1, C15.1, C19.1, D2.4 (VDD), D3.2 (A), J3.1, J4.3, L1.1, L2.2, R9.2, SW1.2, TP1.1, U1.1 (VBAT), U1.20 (VREF+), U1.23 (VDD), U1.35 (VDD), U1.48 (VDD)
+3.3VA: C1.1, C2.1, L1.2, U1.21 (VDDA)
+5V: J1.2, J2.2, J5.2, Q1.3 (D), R14.2, VR1.3 (CW)
BOOT0: C11.2, R2.1, SW1.1, U1.46 (PB8)
CB: C16.1, U2.6 (CB)
DB4: J5.11, U1.28 (PB15)
DB5: J5.12, U1.27 (PB14)
DB6: J5.13, U1.26 (PB13)
DB7: J5.14, U1.25 (PB12)
E: J5.6, U1.29 (PC6)
FB: R9.1, R10.2, U2.4 (FB)
GND: C1.2, C2.2, C3.2, C4.2, C5.2, C6.2, C8.2, C9.2, C10.1, C11.1, C12.1, C13.1, C15.2, C17.1, C19.2, D2.2 (VSS), H1.1, H2.1, H3.1, H4.1, J1.3, J2.3, J3.2, J3.5, J4.5, J4.7, J4.11, J5.1, J5.5, J5.16, Q1.1 (G), R1.1, R2.2, R10.1, R13.1, SW2.1, U1.49 (VSS), U2.1 (GND), VR1.1 (CCW), Y1.2 (G), Y1.4 (G)
HSE_IN: C12.2, U1.5 (PF0), Y1.1
HSE_OUT: R3.1, U1.6 (PF1)
I2C_SCL: J3.3, U1.38 (PA15)
I2C_SDA: J3.4, U1.45 (PB7)
INT_1: J3.7, U1.2 (PC13)
INT_2: J3.6, U1.47 (PB9)
KEY_BLUETOOTH: J2.1, U1.9 (PA1)
LED_DATA_IN: D2.3 (DIN), U1.16 (PC4)
LED_STATUS: D1.2 (A), U1.40 (PC11)
NRST: C10.2, J4.12, SW2.2, U1.7 (PG10)
unnamed: C13.2, R3.2, Y1.3
unnamed: D1.1 (K), R1.2
unnamed: D3.1 (K), R13.2
unnamed: F1.2, FB1.1
unnamed: J5.15, R14.1
unnamed: F1.1, Q1.2 (S)
RS: J5.4, U1.30 (PA8)
STLINK_RX: J4.13, U1.32 (PA10)
STLINK_TX: J4.14, U1.31 (PA9)
SW: C16.2, L2.1, U2.2 (SW)
SWCLK: J4.6, U1.37 (PA14)
SWDIO: J4.4, U1.36 (PA13)
SWO: J4.8, U1.41 (PB3)
TIM3_CH1_PWM: J1.1, U1.14 (PA6)
USART2_RX: J2.4, U1.11 (PA3)
USART2_TX: J2.5, U1.10 (PA2)
V0: J5.3, VR1.2 (WIPER)
VIN: C17.2, FB1.2, U2.3 (VIN), U2.5 (EN)

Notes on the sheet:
STM32 Microcontroler
LCD Screen
Connectors
découplage local
Mounting Holes
Power Circuitry
Cload = 2* (CL-Cstray)
ST LINK

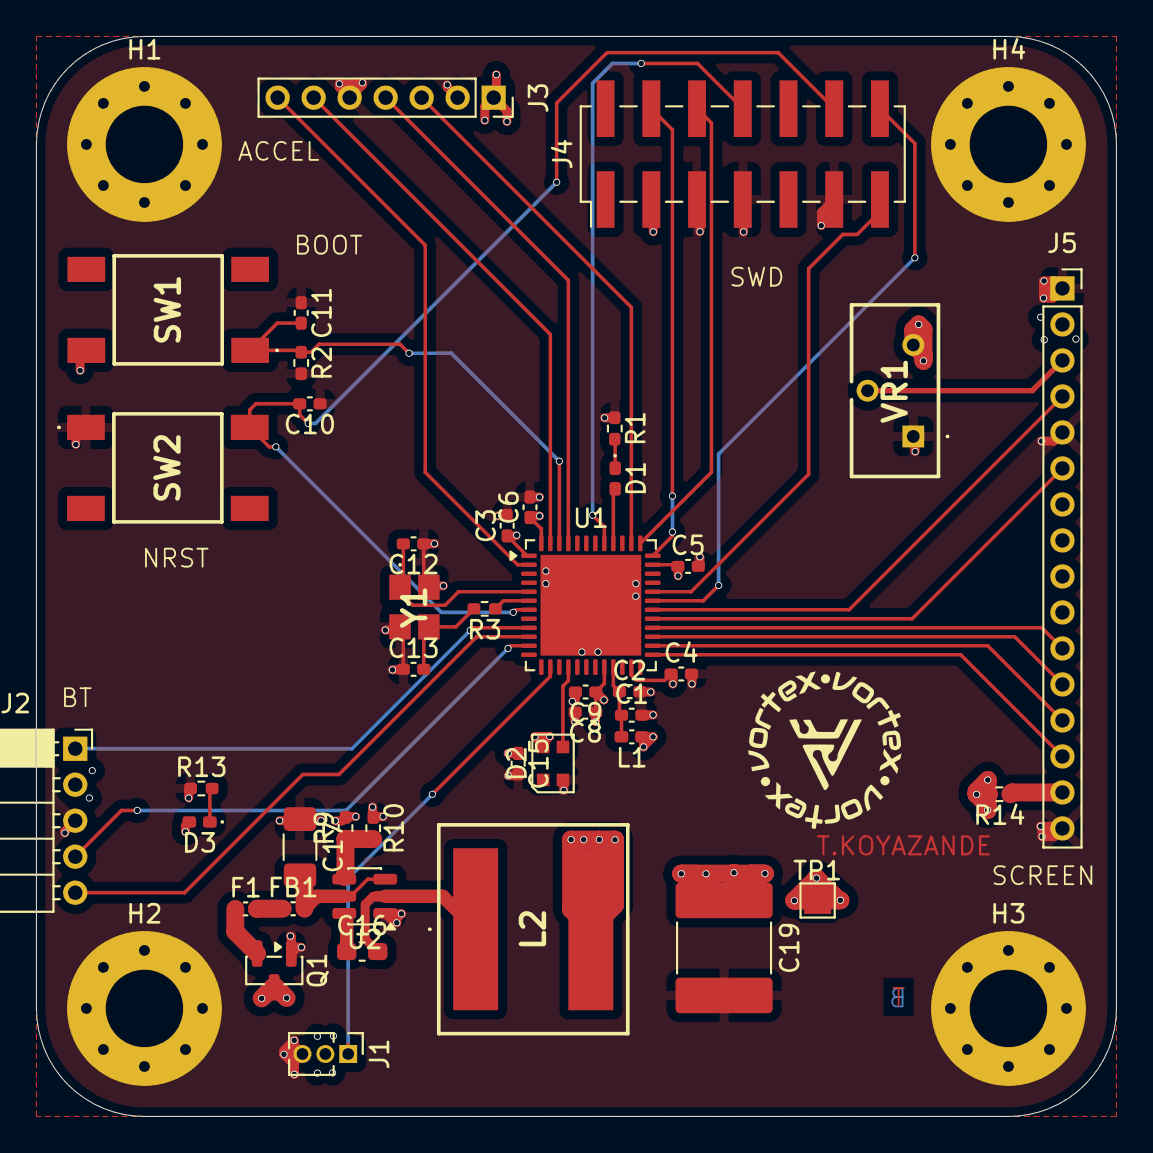
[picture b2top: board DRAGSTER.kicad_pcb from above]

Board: 4 copper layers, 60.0 x 60.0 mm, 47 parts (0 on the bottom side), 40 nets.

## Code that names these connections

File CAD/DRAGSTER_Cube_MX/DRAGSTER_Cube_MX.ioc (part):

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Mcu.Name=STM32G431C(6-8-B)Ux
Mcu.Package=UFQFPN48
Mcu.UserName=STM32G431CBUx
PA1.GPIOParameters=GPIO_Label
PA1.GPIO_Label=KEY
PA1.Signal=GPIO_Output
PA10.Mode=Asynchronous
PA10.Signal=USART1_RX
PA13.Mode=Trace_Asynchronous_SW
PA13.Signal=SYS_JTMS-SWDIO
PA14.Mode=Trace_Asynchronous_SW
PA14.Signal=SYS_JTCK-SWCLK
PA15.Mode=I2C
PA15.Signal=I2C1_SCL
PA2.Mode=Asynchronous
PA2.Signal=USART2_TX
PA3.Mode=Asynchronous
PA3.Signal=USART2_RX
PA6.Signal=S_TIM3_CH1
PA8.GPIOParameters=GPIO_Label
PA8.GPIO_Label=RS
PA8.Signal=GPIO_Output
PA9.Mode=Asynchronous
PA9.Signal=USART1_TX
PB12.GPIOParameters=GPIO_Label
PB12.GPIO_Label=DB7
PB12.Signal=GPIO_Output
PB13.GPIOParameters=GPIO_Label
PB13.GPIO_Label=DB6
PB13.Signal=GPIO_Output
PB14.GPIOParameters=GPIO_Label
PB14.GPIO_Label=DB5
PB14.Signal=GPIO_Output
PB15.GPIOParameters=GPIO_Label
PB15.GPIO_Label=DB4
PB15.Signal=GPIO_Output
PB3.Mode=Trace_Asynchronous_SW
PB3.Signal=SYS_JTDO-SWO
PB7.Mode=I2C
PB7.Signal=I2C1_SDA
PB9.GPIOParameters=GPIO_Label
PB9.GPIO_Label=INT_2
PB9.Signal=GPIO_Input
PC11.GPIOParameters=GPIO_Label
PC11.GPIO_Label=BLUE_USER_LED
PC11.Signal=GPIO_Output
PC13.GPIOParameters=GPIO_Label
PC13.GPIO_Label=INT_1
PC13.Signal=GPIO_Input
PC4.GPIOParameters=GPIO_Label
PC4.GPIO_Label=NEO_PIXEL
PC4.Signal=GPIO_Output
PC6.GPIOParameters=GPIO_Label
PC6.GPIO_Label=E
PC6.Signal=GPIO_Output
PF0-OSC_IN.Mode=HSE-External-Oscillator
PF0-OSC_IN.Signal=RCC_OSC_IN
PF1-OSC_OUT.Mode=HSE-External-Oscillator
PF1-OSC_OUT.Signal=RCC_OSC_OUT
RCC.HSE_VALUE=8000000
RCC.SYSCLKFreq_VALUE=16000000
board=custom

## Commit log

2026-01-15 testing stuff
2026-02-21 deleted useless file
2026-02-21 uploaded cubeM ioc file
2026-02-26 uploaded cubeMX ioc file & pcb
2026-03-04 updated pcb
2026-04-04 reshuffled stuffs a bit
2026-04-20 final update
2026-04-20 well last update
2026-04-20 well last updatee
2026-04-22 well last updateee
2026-04-28 added kicad bom file
2026-04-29 added video
2026-05-05 uploaded TD
2026-05-05 added picture
